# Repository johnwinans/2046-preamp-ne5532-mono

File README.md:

# 2046-preamp-ne5532-mono
A mono preamp for an electret microphone.

These are the source files for a KiCad project featured in a tutorial here:

https://www.youtube.com/playlist?list=PL3by7evD3F51fKkyrUbH-PCdwPCWc9F8a

If you want to make one of these for yourself you can use this design as
it is or and alter it and make it better.  

From time to time, releases of this project are likely to have boards ready 
to order from OshPark.  (I don't get any money from this.  I just think 
they have a good quality and price.)  

https://oshpark.com/profiles/John-Winans

See the schematic for Digikey order numbers of the parts.

Here are some images of the board:

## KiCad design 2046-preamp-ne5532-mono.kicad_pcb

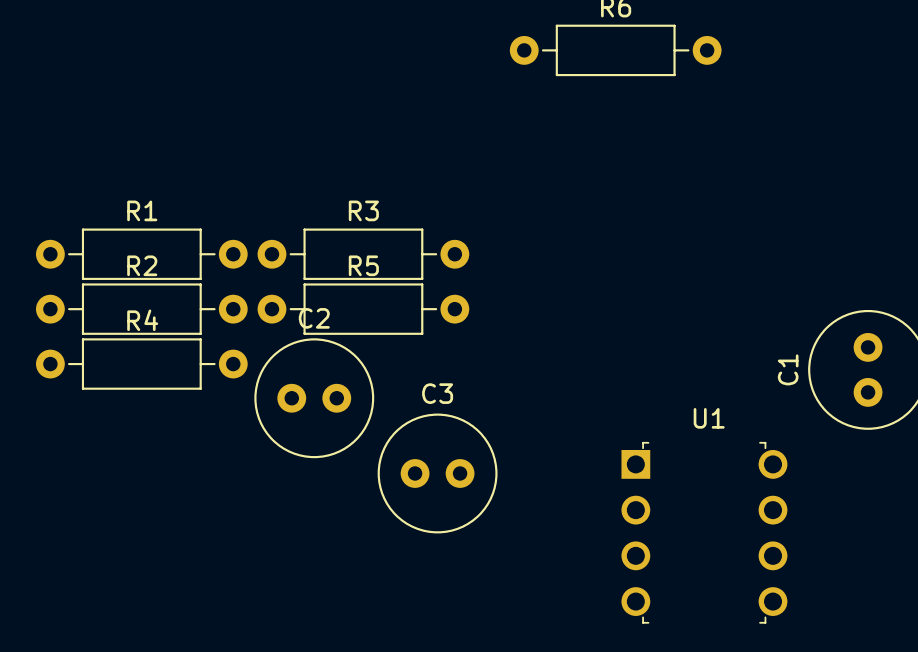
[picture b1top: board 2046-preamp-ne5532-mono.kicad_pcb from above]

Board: 2 copper layers, 10 parts (0 on the bottom side), 8 nets, no tracks yet.

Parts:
C1, C2: 1uF; C_Radial_D6.3mm_H7.0mm_P2.50mm
C3: C; C_Radial_D6.3mm_H7.0mm_P2.50mm
R1, R4, R6: 100K; R_Axial_DIN0207_L6.3mm_D2.5mm_P10.16mm_Horizontal
R2: 2K; R_Axial_DIN0207_L6.3mm_D2.5mm_P10.16mm_Horizontal
R3, R5: 22K; R_Axial_DIN0207_L6.3mm_D2.5mm_P10.16mm_Horizontal
U1: NE5532P; DIP-8_W7.62mm

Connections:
+12V: R3.1, U1.8
GND: C3.1, R5.1, U1.4
unnamed: C1.1, R2.2
unnamed: C2.2, R6.1, U1.7
unnamed: C3.2, R3.2, R5.2, U1.3, U1.5
unnamed: R1.1, R4.1, U1.1
unnamed: R1.2, R2.1, U1.2
unnamed: R4.2, R6.2, U1.6

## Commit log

2019-03-09 As-built drawing of breadboard version.
